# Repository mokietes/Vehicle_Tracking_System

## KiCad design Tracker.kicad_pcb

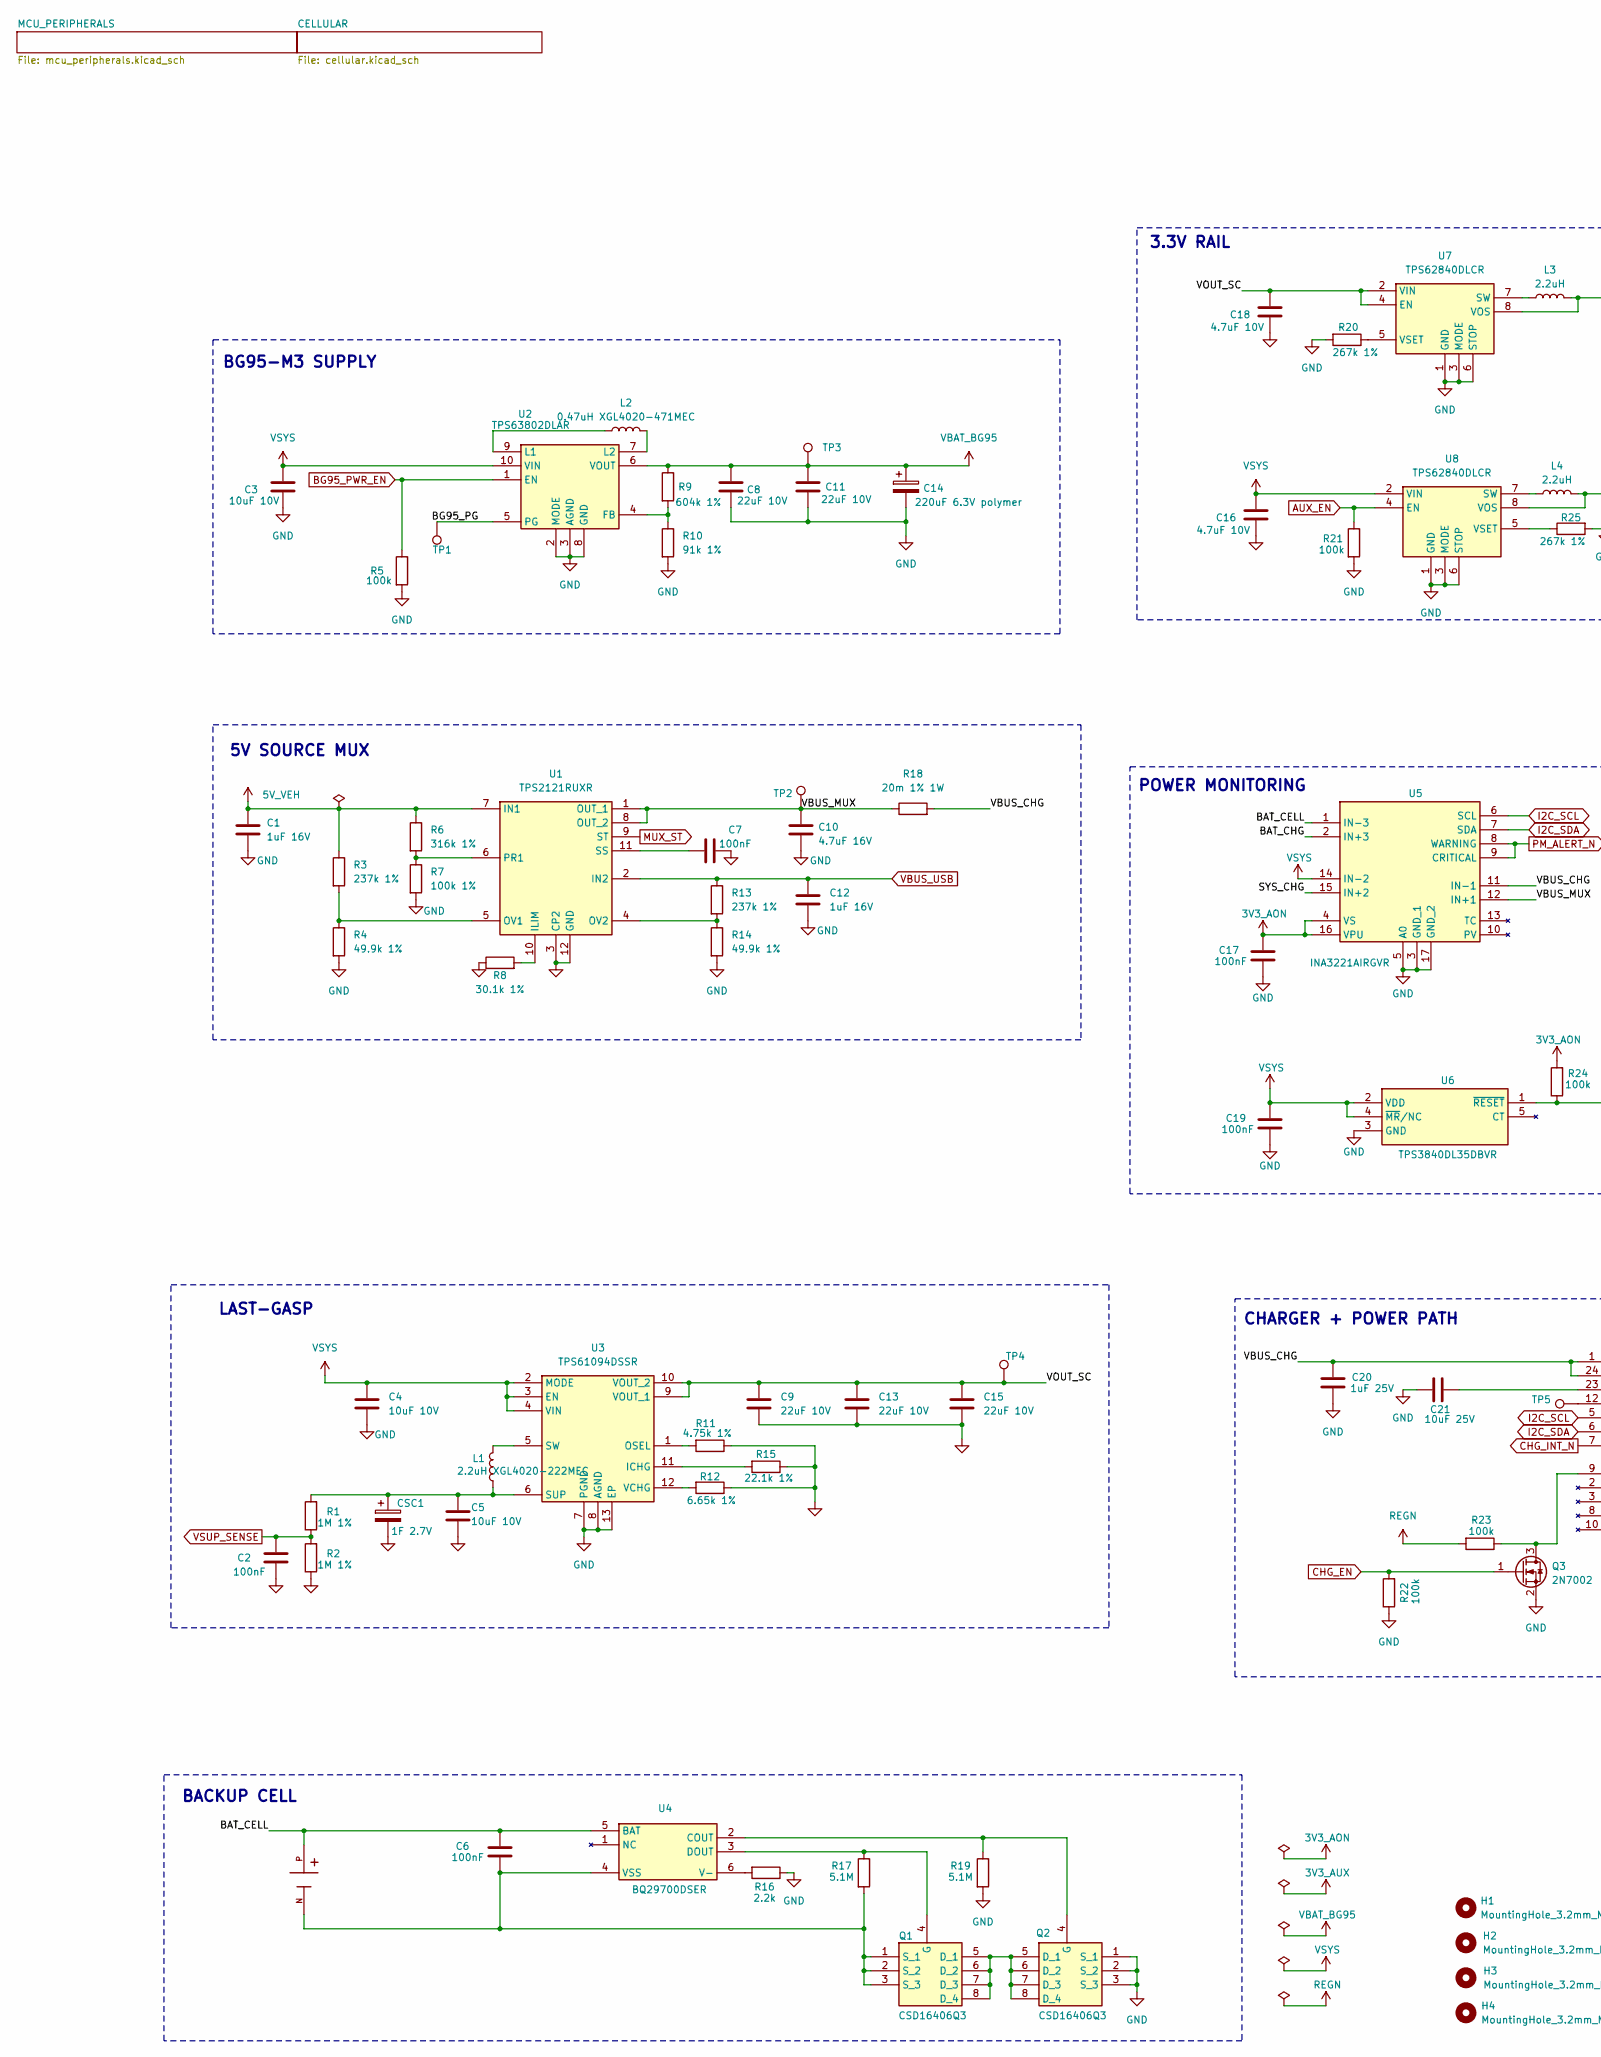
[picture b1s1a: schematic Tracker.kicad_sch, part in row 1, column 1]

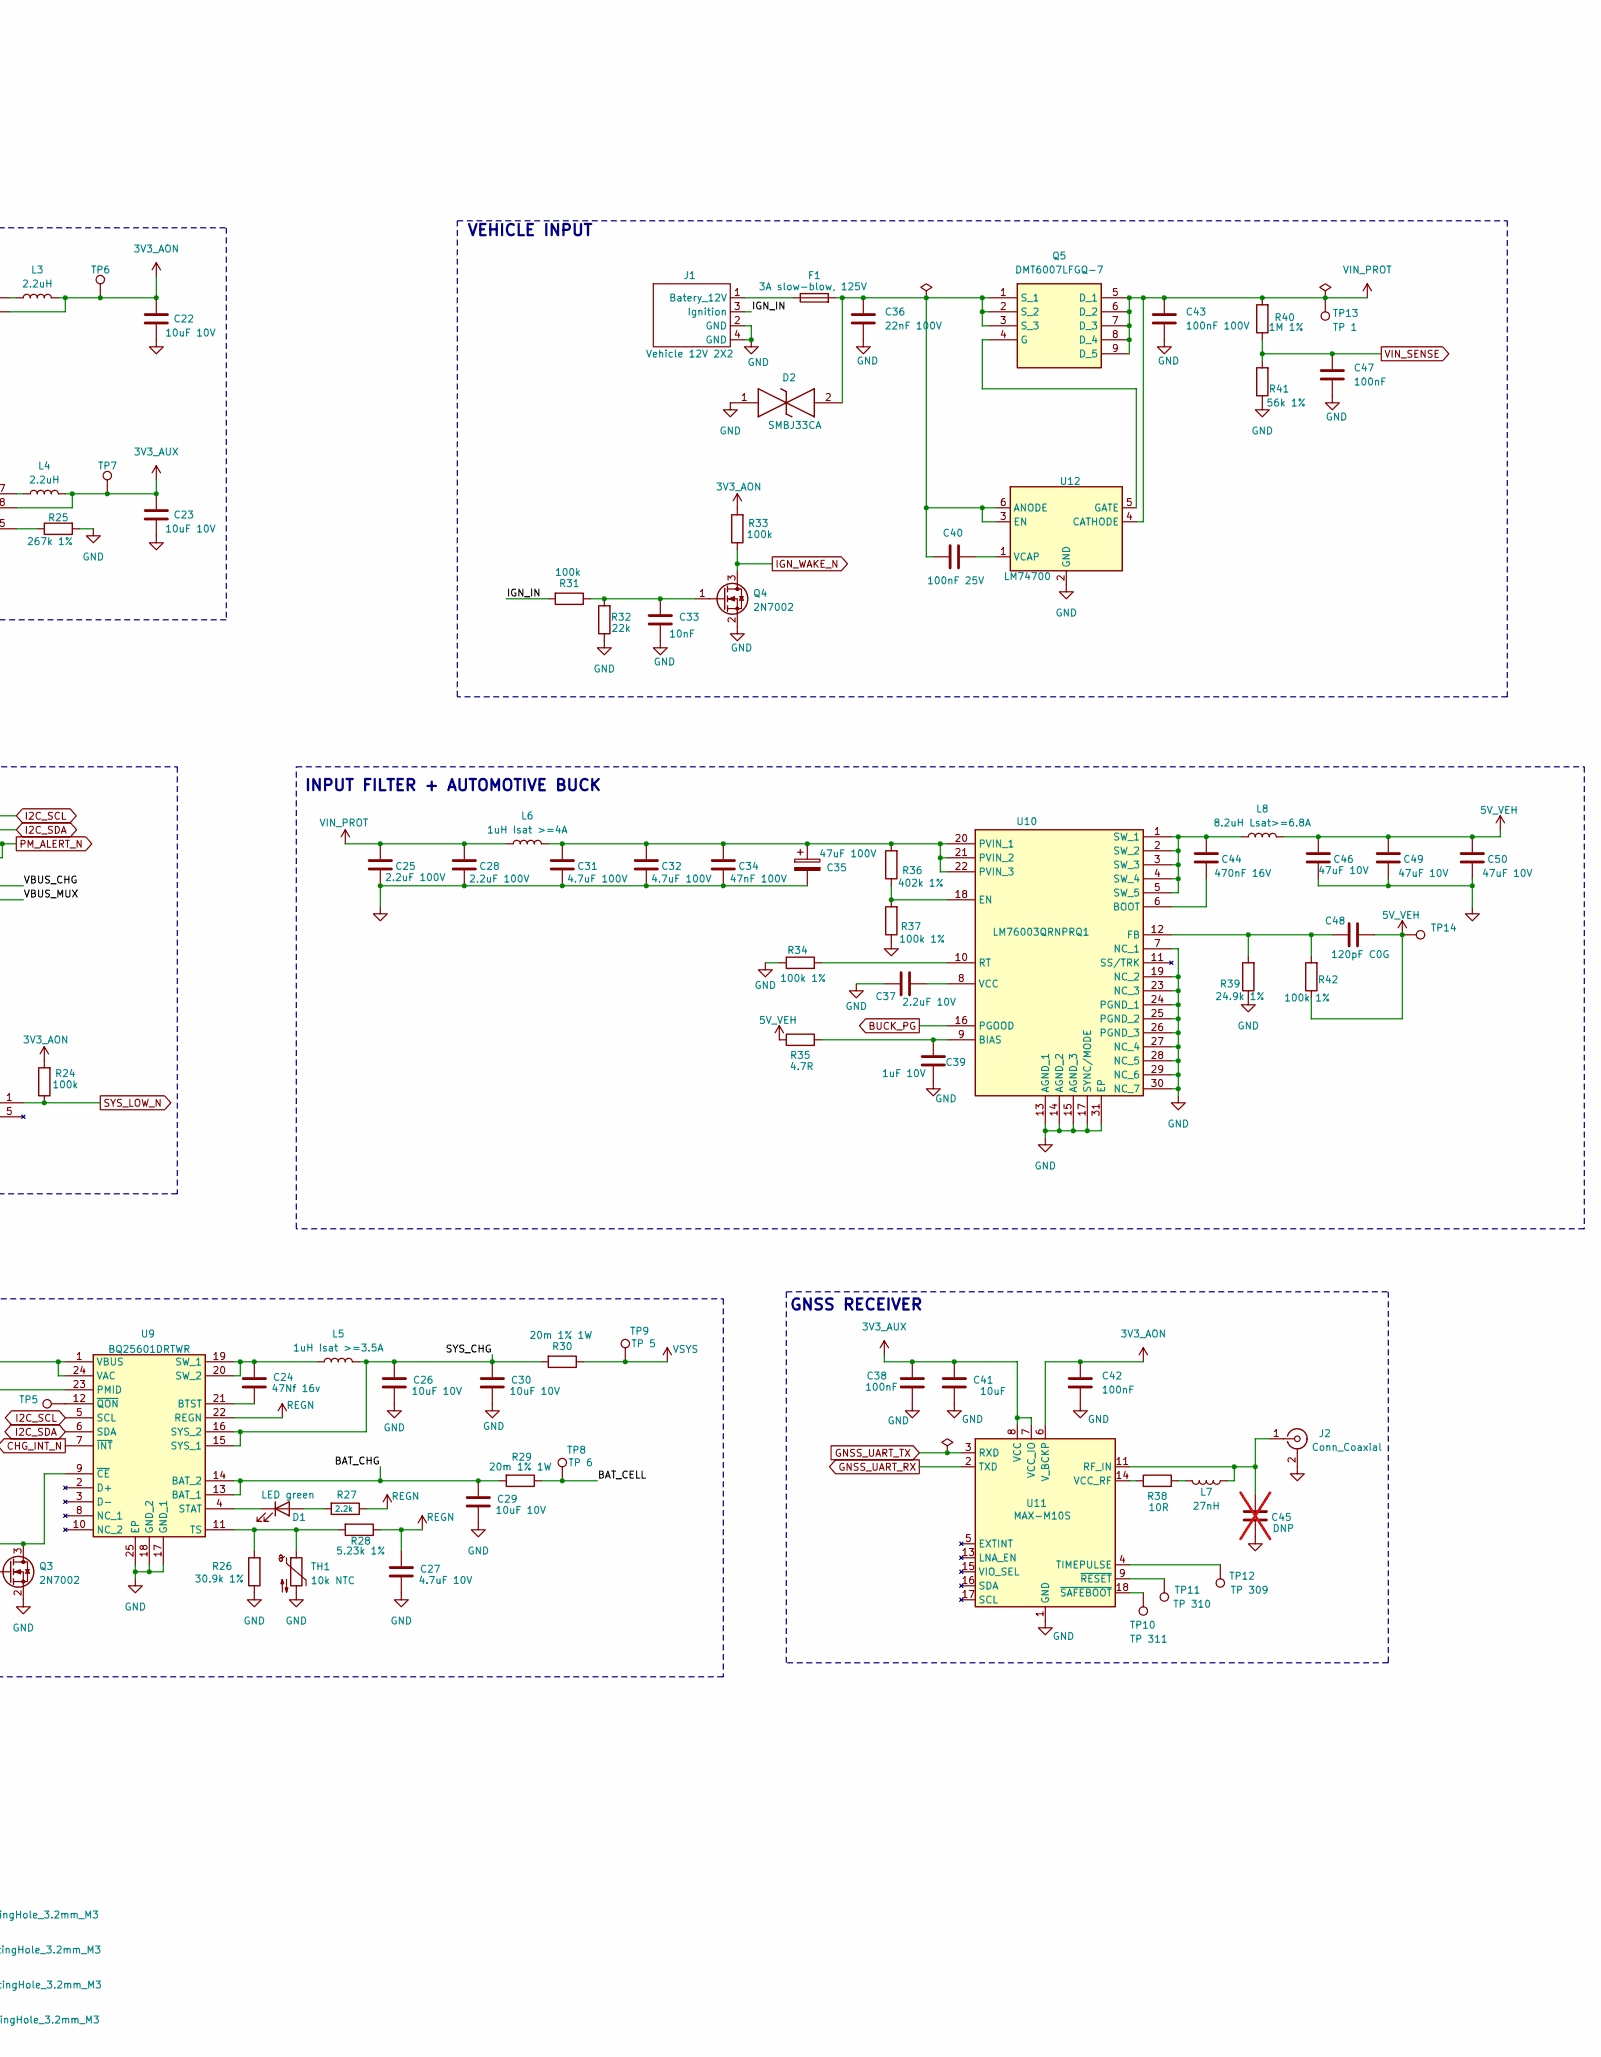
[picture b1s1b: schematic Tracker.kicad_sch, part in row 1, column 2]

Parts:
BT2: BH-18650-PC; BAT_BH-18650-PC; PARTREV 05/17/19
C1, C12: 1uF 16V; C_0603_1608Metric
C2, C6, C7, C17, C19, C47: 100nF; C_0603_1608Metric
C3, C4, C5, C22, C26, C29, C30: 10uF 10V; C_0805_2012Metric
C8, C9, C11, C13, C15: 22uF 10V; C_0805_2012Metric
C10: 4.7uF 16V; C_0805_2012Metric
C14: 220uF 6.3V polymer; CP_EIA-7343-31_Kemet-D
C16, C18: 4.7uF 10V; C_0603_1608Metric
C20: 1uF 25V; C_0603_1608Metric
C21: 10uF 25V; C_1206_3216Metric
C23: 10uF 10V; C_0603_1608Metric
C24: 47Nf 16v; C_0805_2012Metric
C25, C28: 2.2uF 100V; C_1210_3225Metric
C27: 4.7uF 10V; C_0805_2012Metric
C31, C32: 4.7uF 100V; C_1210_3225Metric
C33: 10nF; C_0603_1608Metric
C34: 47nF 100V; C_0603_1608Metric
C35: 47uF 100V; CP_Elec_8x10.5
C36: 22nF 100V; C_0603_1608Metric
C37: 2.2uF 10V; C_0603_1608Metric
C38, C42: 100nF; C_0402_1005Metric
C39: 1uF 10V; C_0603_1608Metric
C40: 100nF 25V; C_0603_1608Metric
C41: 10uF; C_0603_1608Metric
C43: 100nF 100V; C_0603_1608Metric
C44: 470nF 16V; C_0603_1608Metric
C45: DNP; C_0402_1005Metric; not fitted
C46, C49, C50: 47uF 10V; C_1210_3225Metric
C48: 120pF C0G; C_0603_1608Metric
CSC1: 1F 2.7V; CP_Radial_D8.0mm_P3.50mm
D1: LED green; LED_0603_1608Metric
D2: SMBJ33CA; DIONM5436X244N; Manufacturer_Part_Number SMBJ33CA; Mouser Part Number 78-SMBJ33CA
F1: 3A slow-blow, 125V; Fuse_Littelfuse-NANO2-451_453
H1, H2, H3, H4: MountingHole_3.2mm_M3
J1: Vehicle 12V 2X2; Molex_Micro-Fit_3.0_43045-0400_2x02_P3.00mm_Horizontal
J2: Conn_Coaxial; U.FL_Hirose_U.FL-R-SMT-1_Vertical
L1: 2.2uH XGL4020-222MEC; IND_XGL4020_COC-M; MPN XGL4020-222MEC
L2: 0.47uH XGL4020-471MEC; IND_XGL4020_COC-M; MPN XGL4020-471MEC
L3, L4: 2.2uH; L_Murata_DFE201610P
L5: 1uH Isat >=3.5A; L_Coilcraft_XAL5030-XXX
L6: 1uH Isat >=4A; L_Coilcraft_XAL5030-XXX
L7: 27nH; L_0402_1005Metric
L8: 8.2uH Lsat>=6.8A; L_Coilcraft_XAL6030-XXX
Q1, Q2: CSD16406Q3; DQG_VSON-CLIP; Manufacturer_Part_Number CSD16406Q3; Mouser Part Number 595-CSD16406Q3
Q3, Q4: 2N7002; SOT-23
Q5: DMT6007LFGQ-7; DMTH8008LFGQ7; Manufacturer_Part_Number DMT6007LFGQ-7; Mouser Part Number 621-DMT6007LFGQ-7
R1, R2: 1M 1%; R_0603_1608Metric
R3, R13: 237k 1%; R_0603_1608Metric
R4, R14: 49.9k 1%; R_0603_1608Metric
R5, R21, R22, R23, R24, R33: 100k; R_0603_1608Metric
R6: 316k 1%; R_0603_1608Metric
R7, R34, R37, R42: 100k 1%; R_0603_1608Metric
R8: 30.1k 1%; R_0603_1608Metric
R9: 604k 1%; R_0603_1608Metric
R10: 91k 1%; R_0603_1608Metric
R11: 4.75k 1%; R_0603_1608Metric
R12: 6.65k 1%; R_0603_1608Metric
R15: 22.1k 1%; R_0603_1608Metric
R16, R27: 2.2k; R_0603_1608Metric
R17, R19: 5.1M; R_0603_1608Metric
R18, R29, R30: 20m 1% 1W; R_1206_3216Metric
R20, R25: 267k 1%; R_0603_1608Metric
R26: 30.9k 1%; R_0603_1608Metric
R28: 5.23k 1%; R_0603_1608Metric
R31: 100k; R_1206_3216Metric
R32: 22k; R_0603_1608Metric
R35: 4.7R; R_0603_1608Metric
R36: 402k 1%; R_0603_1608Metric
R38: 10R; R_0402_1005Metric
R39: 24.9k 1%; R_0603_1608Metric
R40: 1M 1%; R_1206_3216Metric
R41: 56k 1%; R_0603_1608Metric
TH1: 10k NTC; R_Axial_DIN0204_L3.6mm_D1.6mm_P5.08mm_Horizontal
TP1: TP 208; TestPoint_Pad_D1.5mm
TP2, TP3, TP14: TestPoint; TestPoint_Pad_D1.5mm
TP4, TP6, TP7: TP 9; TestPoint_Pad_D1.5mm
TP5: TestPoint_Pad_D1.5mm
TP8: TP 6; TestPoint_Pad_D1.5mm
TP9: TP 5; TestPoint_Pad_D1.5mm
TP10: TP 311; TestPoint_Pad_D1.5mm
TP11: TP 310; TestPoint_Pad_D1.5mm
TP12: TP 309; TestPoint_Pad_D1.5mm
TP13: TP 1; TestPoint_Pad_D1.5mm
U1: TPS2121RUXR; Manufacturer_Part_Number TPS2121RUXR; Mouser Part Number 595-TPS2121RUXR
U2: TPS63802DLAR; Manufacturer_Part_Number TPS63802DLAR; Mouser Part Number 595-TPS63802DLAR
U3: TPS61094DSSR; SON50P200X300X80-13N-D; Manufacturer_Part_Number TPS61094DSSR; Mouser Part Number 595-TPS61094DSSR
U4: BQ29700DSER; SON50P150X150X80-6N; Manufacturer_Part_Number BQ29700DSER; Mouser Part Number 595-BQ29700DSER
U5: INA3221AIRGVR; QFN65P400X400X100-17N-D; Manufacturer_Part_Number INA3221AIRGVR; Mouser Part Number 595-INA3221AIRGVR
U6: TPS3840DL35DBVR; SOT95P280X145-5N; Manufacturer_Part_Number TPS3840DL35DBVR; Mouser Part Number 595-TPS3840DL35DBVR
U7, U8: TPS62840DLCR; SON50P150X200X100-8N-D; Manufacturer_Part_Number TPS62840DLCR; Mouser Part Number 595-TPS62840DLCR
U9: BQ25601DRTWR; QFN50P400X400X80-25N-D; Manufacturer_Part_Number BQ25601DRTWR; Mouser Part Number 595-BQ25601DRTWR
U10: LM76003QRNPRQ1; Manufacturer_Part_Number LM76003QRNPRQ1; Mouser Part Number 595-LM76003QRNPRQ1
U11: MAX-M10S; ublox_MAX
U12: LM74700; SOT-23-6

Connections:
3V3_AON: C17.1, C22.1, C42.1, L3.2, R24.2, R33.2, TP6.1 (1_1), U5.4 (VS), U5.16 (VPU), U7.8 (VOS), U11.6 (V_BCKP); also elsewhere on the board
3V3_AUX: C23.1, C38.1, C41.1, L4.2, TP7.1 (1_1), U8.8 (VOS), U11.7 (VCC_IO), U11.8 (VCC); also elsewhere on the board
5V_VEH: C1.1, C46.2, C48.2, C49.2, C50.2, L8.2, R3.1, R6.1, R35.1, R42.1, TP14.1 (1_1), U1.7 (IN1)
/BAT_CELL: BT2.P, C6.1, R29.1, TP8.1 (1_1), U4.5 (BAT), U5.1 (IN-3)
/BAT_CHG: C29.1, R29.2, U5.2 (IN+3), U9.13 (BAT_1), U9.14 (BAT_2)
/BG95_PG: TP1.1 (1_1), U2.5 (PG)
/IGN_IN: J1.3 (Ignition), R31.2
/SYS_CHG: C26.1, C30.1, L5.2, R30.2, U5.15 (IN+2), U9.15 (SYS_1), U9.16 (SYS_2)
/VBUS_CHG: C20.1, R18.2, U5.11 (IN-1), U9.1 (VBUS), U9.24 (VAC)
/VBUS_MUX: C10.1, R18.1, TP2.1 (1_1), U1.1 (OUT_1), U1.8 (OUT_2), U5.12 (IN+1)
/VOUT_SC: C9.1, C13.1, C15.1, C18.1, TP4.1 (1_1), U3.9 (VOUT_1), U3.10 (VOUT_2), U7.2 (VIN), U7.4 (EN)
AUX_EN: R21.1, U8.4 (EN); also elsewhere on the board
BG95_PWR_EN: R5.1, U2.1 (EN); also elsewhere on the board
BUCK_PG: U10.16 (PGOOD); also elsewhere on the board
CHG_EN: Q3.1 (G), R22.2; also elsewhere on the board
CHG_INT_N: U9.7 (~INT); also elsewhere on the board
GND: C1.2, C2.2, C3.2, C4.2, C5.2, C7.2, C8.2, C9.2, C10.2, C11.2, C12.2, C13.2, C14.2, C15.2, C16.2, C17.2, C18.2, C19.2, C20.2, C21.1, C22.2, C23.2, C25.1, C26.2, C27.2, C28.1, C29.2, C30.2, C31.1, C32.1, C33.2, C34.1, C35.2, C36.2, C37.1, C38.2, C39.2, C41.2, C42.2, C43.2, C45.1, C46.1, C47.2, C49.1, C50.1, CSC1.2, D2.1, J1.2 (GND), J1.4 (GND), J2.2 (Ext), Q2.1 (S_1), Q2.2 (S_2), Q2.3 (S_3), Q3.2 (S), Q4.2 (S), R2.1, R4.2, R5.2, R7.2, R8.1, R10.2, R11.1, R12.1, R14.2, R15.1, R16.1, R19.2, R20.2, R21.2, R22.1, R25.2, R26.1, R32.1, R34.1, R37.1, R39.1, R41.1, TH1.2, U1.3 (CP2), U1.12 (GND), U2.2 (MODE), U2.3 (AGND), U2.8 (GND), U3.7 (PGND), U3.8 (AGND), U3.13 (EP), U5.3 (GND_1), U5.5 (A0), U5.17 (GND_2), U6.3 (GND), U7.1 (GND), U7.3 (MODE), U7.6 (STOP), U8.1 (GND), U8.3 (MODE), U8.6 (STOP), U9.17 (GND_1), U9.18 (GND_2), U9.25 (EP), U10.7 (NC_1), U10.13 (AGND_1), U10.14 (AGND_2), U10.15 (AGND_3), U10.17 (SYNC/MODE), U10.19 (NC_2), U10.23 (NC_3), U10.24 (PGND_1), U10.25 (PGND_2), U10.26 (PGND_3), U10.27 (NC_4), U10.28 (NC_5), U10.29 (NC_6), U10.30 (NC_7), U10.31 (EP), U11.1 (GND), U11.10 (GND), U11.12 (GND), U12.2 (GND); also elsewhere on the board
GNSS_UART_RX: U11.2 (TXD); also elsewhere on the board
GNSS_UART_TX: U11.3 (RXD); also elsewhere on the board
I2C_SCL: U5.6 (SCL), U9.5 (SCL); also elsewhere on the board
I2C_SDA: U5.7 (SDA), U9.6 (SDA); also elsewhere on the board
IGN_WAKE_N: Q4.3 (D), R33.1; also elsewhere on the board
MUX_ST: U1.9 (ST); also elsewhere on the board
unnamed: D1.2 (A), R27.2
unnamed: D1.1 (K), U9.4 (STAT)
unnamed: F1.1, J1.1 (Batery_12V)
unnamed: C45.2, J2.1 (In), L7.1, U11.11 (RF_IN)
unnamed: L7.2, R38.2
unnamed: Q1.5 (D_1), Q1.6 (D_2), Q1.7 (D_3), Q1.8 (D_4), Q2.5 (D_1), Q2.6 (D_2), Q2.7 (D_3), Q2.8 (D_4)
unnamed: Q1.4 (G), R17.1, U4.3 (DOUT)
unnamed: BT2.N, C6.2, Q1.1 (S_1), Q1.2 (S_2), Q1.3 (S_3), R17.2, U4.4 (VSS)
unnamed: Q2.4 (G), R19.1, U4.2 (COUT)
unnamed: Q3.3 (D), R23.1, U9.9 (~CE)
unnamed: C33.1, Q4.1 (G), R31.1, R32.2
unnamed: Q5.4 (G), U12.5 (GATE)
unnamed: C36.1, C40.1, D2.2, F1.2, Q5.1 (S_1), Q5.2 (S_2), Q5.3 (S_3), U12.3 (EN), U12.6 (ANODE)
unnamed: R8.2, U1.10 (ILIM)
unnamed: R3.2, R4.1, U1.5 (OV1)
unnamed: R13.2, R14.1, U1.4 (OV2)
unnamed: R6.2, R7.1, U1.6 (PR1)
unnamed: C7.1, U1.11 (SS)
unnamed: R9.2, R10.1, U2.4 (FB)
unnamed: L2.1, U2.9 (L1)
unnamed: L2.2, U2.7 (L2)
unnamed: R15.2, U3.11 (ICHG)
unnamed: R11.2, U3.1 (OSEL)
unnamed: C5.1, CSC1.1, L1.2, R1.2, U3.6 (SUP)
unnamed: L1.1, U3.5 (SW)
unnamed: R12.2, U3.12 (VCHG)
unnamed: R16.2, U4.6 (V-)
unnamed: L3.1, U7.7 (SW)
unnamed: R20.1, U7.5 (VSET)
unnamed: L4.1, U8.7 (SW)
unnamed: R25.1, U8.5 (VSET)
unnamed: C24.2, U9.21 (BTST)
unnamed: C21.2, U9.23 (PMID)
unnamed: C24.1, L5.1, U9.19 (SW_1), U9.20 (SW_2)
unnamed: R26.2, R28.2, TH1.1, U9.11 (TS)
unnamed: TP5.1 (1_1), U9.12 (~QON)
unnamed: C39.1, R35.2, U10.9 (BIAS)
unnamed: C44.1, U10.6 (BOOT)
unnamed: R36.1, R37.2, U10.18 (EN)
unnamed: C48.1, R39.2, R42.2, U10.12 (FB)
unnamed: C31.2, C32.2, C34.2, C35.1, L6.2, R36.2, U10.20 (PVIN_1), U10.21 (PVIN_2), U10.22 (PVIN_3)
unnamed: R34.2, U10.10 (RT)
unnamed: C44.2, L8.1, U10.1 (SW_1), U10.2 (SW_2), U10.3 (SW_3), U10.4 (SW_4), U10.5 (SW_5)
unnamed: C37.2, U10.8 (VCC)
unnamed: TP12.1 (1_1), U11.4 (TIMEPULSE)
unnamed: R38.1, U11.14 (VCC_RF)
unnamed: TP11.1 (1_1), U11.9 (~RESET)
unnamed: TP10.1 (1_1), U11.18 (~SAFEBOOT)
unnamed: C40.2, U12.1 (VCAP)
PM_ALERT_N: U5.8 (WARNING), U5.9 (CRITICAL); also elsewhere on the board
REGN: C27.1, R23.2, R27.1, R28.1, U9.22 (REGN)
SYS_LOW_N: R24.1, U6.1 (~RESET); also elsewhere on the board
VBAT_BG95: C8.1, C11.1, C14.1, R9.1, TP3.1 (1_1), U2.6 (VOUT); also elsewhere on the board
VBUS_USB: C12.1, R13.1, U1.2 (IN2); also elsewhere on the board
VIN_PROT: C25.2, C28.2, C43.1, L6.1, Q5.5 (D_1), Q5.6 (D_2), Q5.7 (D_3), Q5.8 (D_4), Q5.9 (D_5), R40.2, TP13.1 (1_1), U12.4 (CATHODE)
VIN_SENSE: C47.1, R40.1, R41.2; also elsewhere on the board
VSUP_SENSE: C2.1, R1.1, R2.2; also elsewhere on the board
VSYS: C3.1, C4.1, C16.1, C19.1, R30.1, TP9.1 (1_1), U2.10 (VIN), U3.2 (MODE), U3.3 (EN), U3.4 (VIN), U5.14 (IN-2), U6.2 (VDD), U6.4 (~MR/NC), U8.2 (VIN)

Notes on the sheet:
POWER MONITORING
BACKUP CELL
CHARGER + POWER PATH
BG95-M3 SUPPLY
VEHICLE INPUT
GNSS RECEIVER
3.3V RAIL
5V SOURCE MUX
LAST-GASP
INPUT FILTER + AUTOMOTIVE BUCK

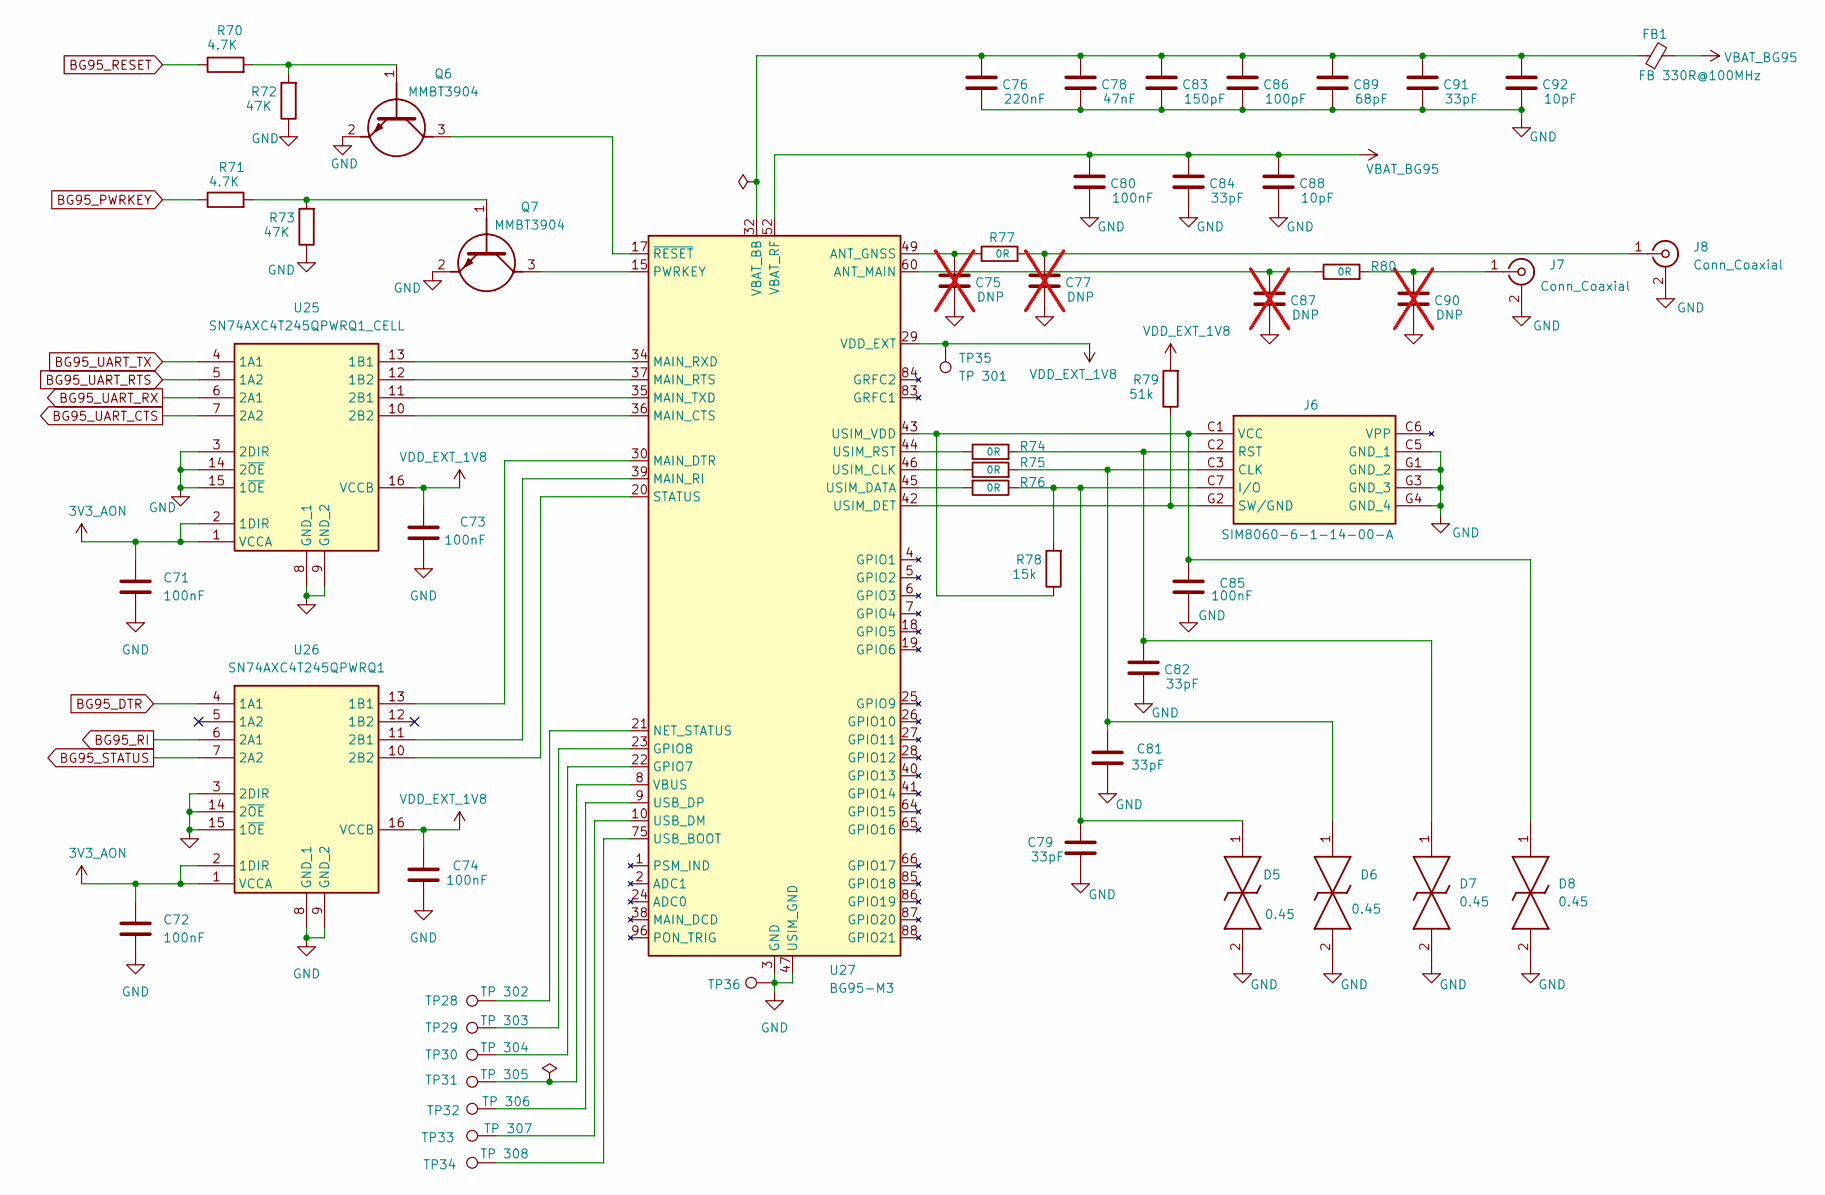
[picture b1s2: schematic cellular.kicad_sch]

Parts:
C71, C72, C73, C74, C80, C85: 100nF; C_0402_1005Metric
C75, C77, C87, C90: DNP; C_0402_1005Metric; not fitted
C76: 220nF; C_0402_1005Metric
C78: 47nF; C_0402_1005Metric
C79, C81, C82, C84, C91: 33pF; C_0402_1005Metric
C83: 150pF; C_0402_1005Metric
C86: 100pF; C_0402_1005Metric
C88, C92: 10pF; C_0402_1005Metric
C89: 68pF; C_0402_1005Metric
D5, D6, D7, D8: TPD1E10B06DPYR; Manufacturer_Part_Number TPD1E10B06DPYR; Mouser Part Number 595-TPD1E10B06DPYR
FB1: FB 330R@100MHz; L_0402_1005Metric
J6: SIM8060-6-1-14-00-A; SIM8060611400A; Mouser Part Number 640-SIM8060611400A
J7, J8: Conn_Coaxial; U.FL_Hirose_U.FL-R-SMT-1_Vertical
Q6, Q7: MMBT3904; SOT95P230X110-3N; Manufacturer_Part_Number MMBT3904
R70, R71: 4.7K; R_0402_1005Metric
R72, R73: 47K; R_0402_1005Metric
R74, R75, R76, R77, R80: 0R; R_0402_1005Metric
R78: 15k; R_0402_1005Metric
R79: 51k; R_0402_1005Metric
TP28: TP 302; TestPoint_Pad_D1.5mm
TP29: TP 303; TestPoint_Pad_D1.5mm
TP30: TP 304; TestPoint_Pad_D1.5mm
TP31: TP 305; TestPoint_Pad_D1.5mm
TP32: TP 306; TestPoint_Pad_D1.5mm
TP33: TP 307; TestPoint_Pad_D1.5mm
TP34: TP 308; TestPoint_Pad_D1.5mm
TP35: TP 301; TestPoint_Pad_D1.5mm
TP36: TestPoint_Pad_D1.5mm
U25: SN74AXC4T245QPWRQ1_CELL; SOP65P640X120-16N; Mouser Part Number 595-74AXC4T245QPWRQ1
U26: SN74AXC4T245QPWRQ1; SOP65P640X120-16N; Mouser Part Number 595-74AXC4T245QPWRQ1
U27: BG95-M3; Quectel_BG95

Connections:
3V3_AON: C71.1, C72.1, U25.1 (VCCA), U25.2 (1DIR), U26.1 (VCCA), U26.2 (1DIR); also elsewhere on the board
BG95_DTR: U26.4 (1A1); also elsewhere on the board
BG95_PWRKEY: R71.1; also elsewhere on the board
BG95_RESET: R70.1; also elsewhere on the board
BG95_RI: U26.6 (2A1); also elsewhere on the board
BG95_STATUS: U26.7 (2A2); also elsewhere on the board
BG95_UART_CTS: U25.7 (2A2); also elsewhere on the board
BG95_UART_RTS: U25.5 (1A2); also elsewhere on the board
BG95_UART_RX: U25.6 (2A1); also elsewhere on the board
BG95_UART_TX: U25.4 (1A1); also elsewhere on the board
GND: C71.2, C72.2, C73.2, C74.2, C75.1, C76.1, C77.1, C78.1, C79.1, C80.1, C81.2, C82.1, C83.1, C84.1, C85.2, C86.1, C87.1, C88.1, C89.1, C90.1, C91.1, C92.1, D5.2, D6.2, D7.2, D8.2, J6.C5 (GND_1), J6.G1 (GND_2), J6.G3 (GND_3), J6.G4 (GND_4), J7.2 (Ext), J8.2 (Ext), Q6.2 (E), Q7.2 (E), R72.1, R73.1, TP36.1 (1_1), U25.3 (2DIR), U25.8 (GND_1), U25.9 (GND_2), U25.14 (2~OE), U25.15 (1~OE), U26.3 (2DIR), U26.8 (GND_1), U26.9 (GND_2), U26.14 (2~OE), U26.15 (1~OE), U27.3 (GND), U27.31 (GND), U27.47 (USIM_GND), U27.48 (GND), U27.50 (GND), U27.54 (GND), U27.55 (GND), U27.58 (GND), U27.59 (GND), U27.61 (GND), U27.62 (GND), U27.67 (GND), U27.68 (GND), U27.69 (GND), U27.70 (GND), U27.71 (GND), U27.72 (GND), U27.73 (GND), U27.74 (GND), U27.79 (GND), U27.80 (GND), U27.81 (GND), U27.82 (GND), U27.89 (GND), U27.90 (GND), U27.91 (GND), U27.100 (GND), U27.101 (GND), U27.102 (GND); also elsewhere on the board
unnamed: C76.2, C78.2, C83.2, C86.2, C89.2, C91.2, C92.2, FB1.1, U27.32 (VBAT_BB), U27.33 (VBAT_BB)
unnamed: C81.1, D6.1, J6.C3 (CLK), R75.2
unnamed: C79.2, D5.1, J6.C7 (I/O), R76.1, R78.2
unnamed: C82.2, D7.1, J6.C2 (RST), R74.2
unnamed: J6.G2 (SW/GND), R79.1, U27.42 (USIM_DET)
unnamed: C85.1, D8.1, J6.C1 (VCC), R78.1, U27.43 (USIM_VDD)
unnamed: C90.2, J7.1 (In), R80.2
unnamed: C77.2, J8.1 (In), R77.2
unnamed: Q6.1 (B), R70.2, R72.2
unnamed: Q6.3 (C), U27.17 (~RESET)
unnamed: Q7.1 (B), R71.2, R73.2
unnamed: Q7.3 (C), U27.15 (PWRKEY)
unnamed: U25.13 (1B1), U27.34 (MAIN_RXD)
unnamed: U25.12 (1B2), U27.37 (MAIN_RTS)
unnamed: U25.11 (2B1), U27.35 (MAIN_TXD)
unnamed: U25.10 (2B2), U27.36 (MAIN_CTS)
unnamed: U26.13 (1B1), U27.30 (MAIN_DTR)
unnamed: U26.11 (2B1), U27.39 (MAIN_RI)
unnamed: U26.10 (2B2), U27.20 (STATUS)
unnamed: C75.2, R77.1, U27.49 (ANT_GNSS)
unnamed: C87.2, R80.1, U27.60 (ANT_MAIN)
unnamed: TP30.1 (1_1), U27.22 (GPIO7)
unnamed: TP29.1 (1_1), U27.23 (GPIO8)
unnamed: TP28.1 (1_1), U27.21 (NET_STATUS)
unnamed: TP34.1 (1_1), U27.75 (USB_BOOT)
unnamed: TP33.1 (1_1), U27.10 (USB_DM)
unnamed: TP32.1 (1_1), U27.9 (USB_DP)
unnamed: R75.1, U27.46 (USIM_CLK)
unnamed: R76.2, U27.45 (USIM_DATA)
unnamed: R74.1, U27.44 (USIM_RST)
unnamed: TP31.1 (1_1), U27.8 (VBUS)
VBAT_BG95: C80.2, C84.2, C88.2, FB1.2, U27.52 (VBAT_RF), U27.53 (VBAT_RF); also elsewhere on the board
VDD_EXT_1V8: C73.1, C74.1, R79.2, TP35.1 (1_1), U25.16 (VCCB), U26.16 (VCCB), U27.29 (VDD_EXT)
